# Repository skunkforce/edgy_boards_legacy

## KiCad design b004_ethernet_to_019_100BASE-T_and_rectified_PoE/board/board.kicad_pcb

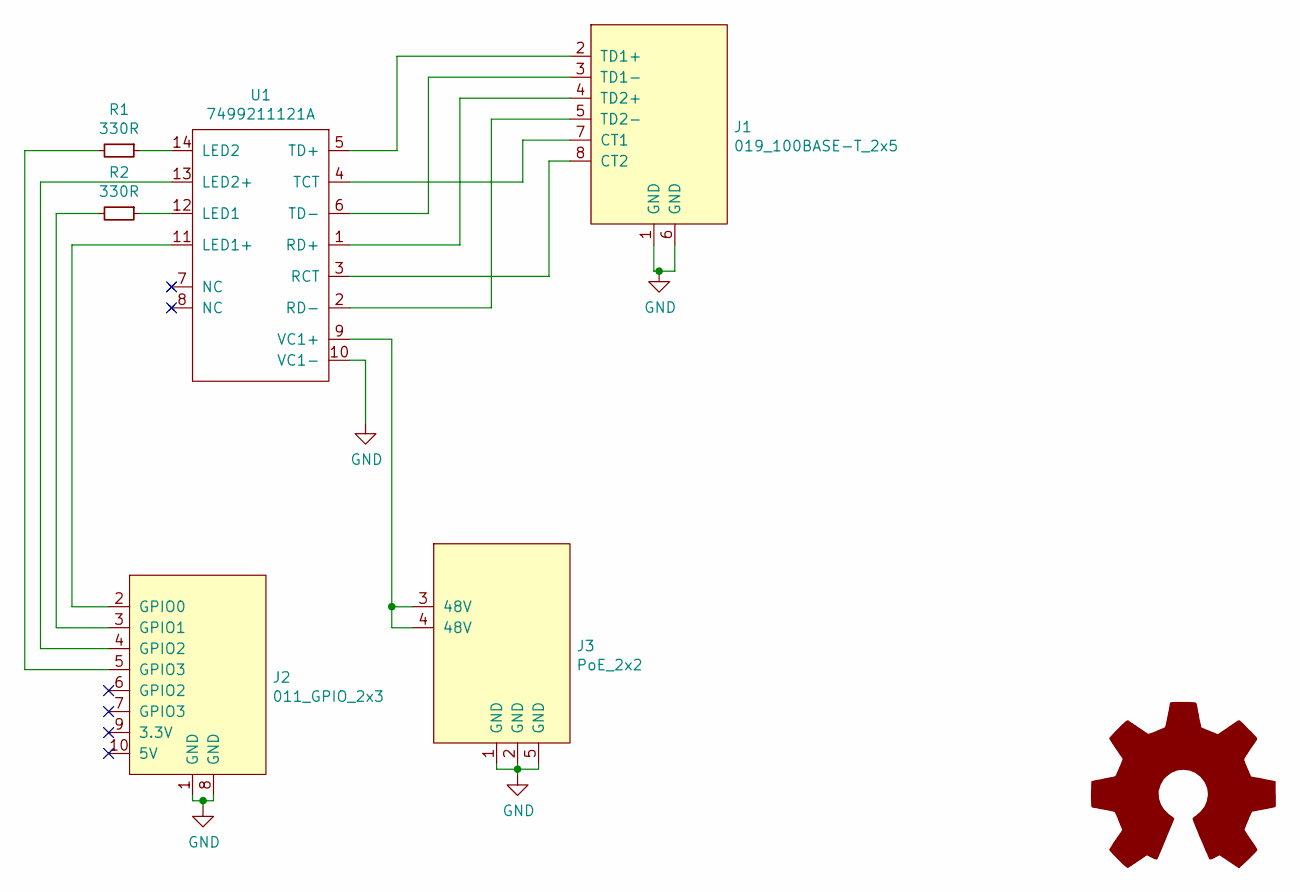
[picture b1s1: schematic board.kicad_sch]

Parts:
J1: 019_100BASE-T_2x5; on_edge_2x05_device
J2: 011_GPIO_2x3; on_edge_2x05_device
J3: PoE_2x2; on_edge_2x05_host
R1, R2: 330R; R_0603_1608Metric
U1: 7499211121A; MPN 7499211121A
l1: Logo_Open_Hardware_Large; OSHW-Logo2_7.3x6mm_SilkScreen

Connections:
GND: J1.1 (GND), J1.6 (GND), J2.1 (GND), J2.8 (GND), J3.1 (GND), J3.2 (GND), J3.5 (GND), U1.10 (VC1-)
unnamed: J1.2 (TD1+), U1.5 (TD+)
unnamed: J1.3 (TD1-), U1.6 (TD-)
unnamed: J1.4 (TD2+), U1.1 (RD+)
unnamed: J1.5 (TD2-), U1.2 (RD-)
unnamed: J1.7 (CT1), U1.4 (TCT)
unnamed: J1.8 (CT2), U1.3 (RCT)
unnamed: J2.2 (GPIO0), U1.11 (LED1+)
unnamed: J2.3 (GPIO1), R2.2
unnamed: J2.4 (GPIO2), U1.13 (LED2+)
unnamed: J2.5 (GPIO3), R1.2
unnamed: J3.3 (48V), J3.4 (48V), U1.9 (VC1+)
unnamed: R1.1, U1.14 (LED2)
unnamed: R2.1, U1.12 (LED1)

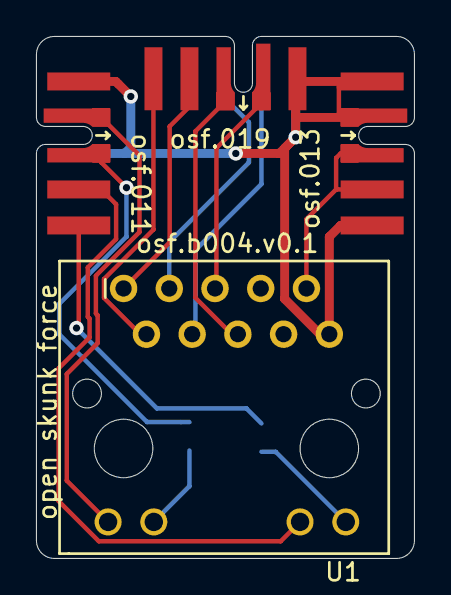
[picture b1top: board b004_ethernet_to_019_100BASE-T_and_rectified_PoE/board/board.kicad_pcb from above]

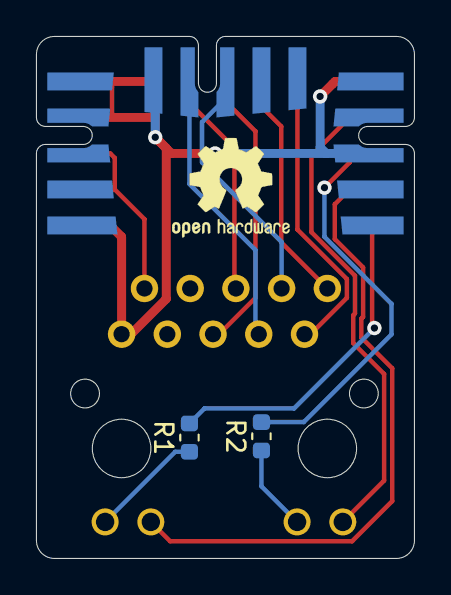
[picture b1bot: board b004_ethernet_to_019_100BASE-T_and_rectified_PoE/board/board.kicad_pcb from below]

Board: 2 copper layers, 21.0 x 29.0 mm, 7 parts (3 on the bottom side), 14 nets.

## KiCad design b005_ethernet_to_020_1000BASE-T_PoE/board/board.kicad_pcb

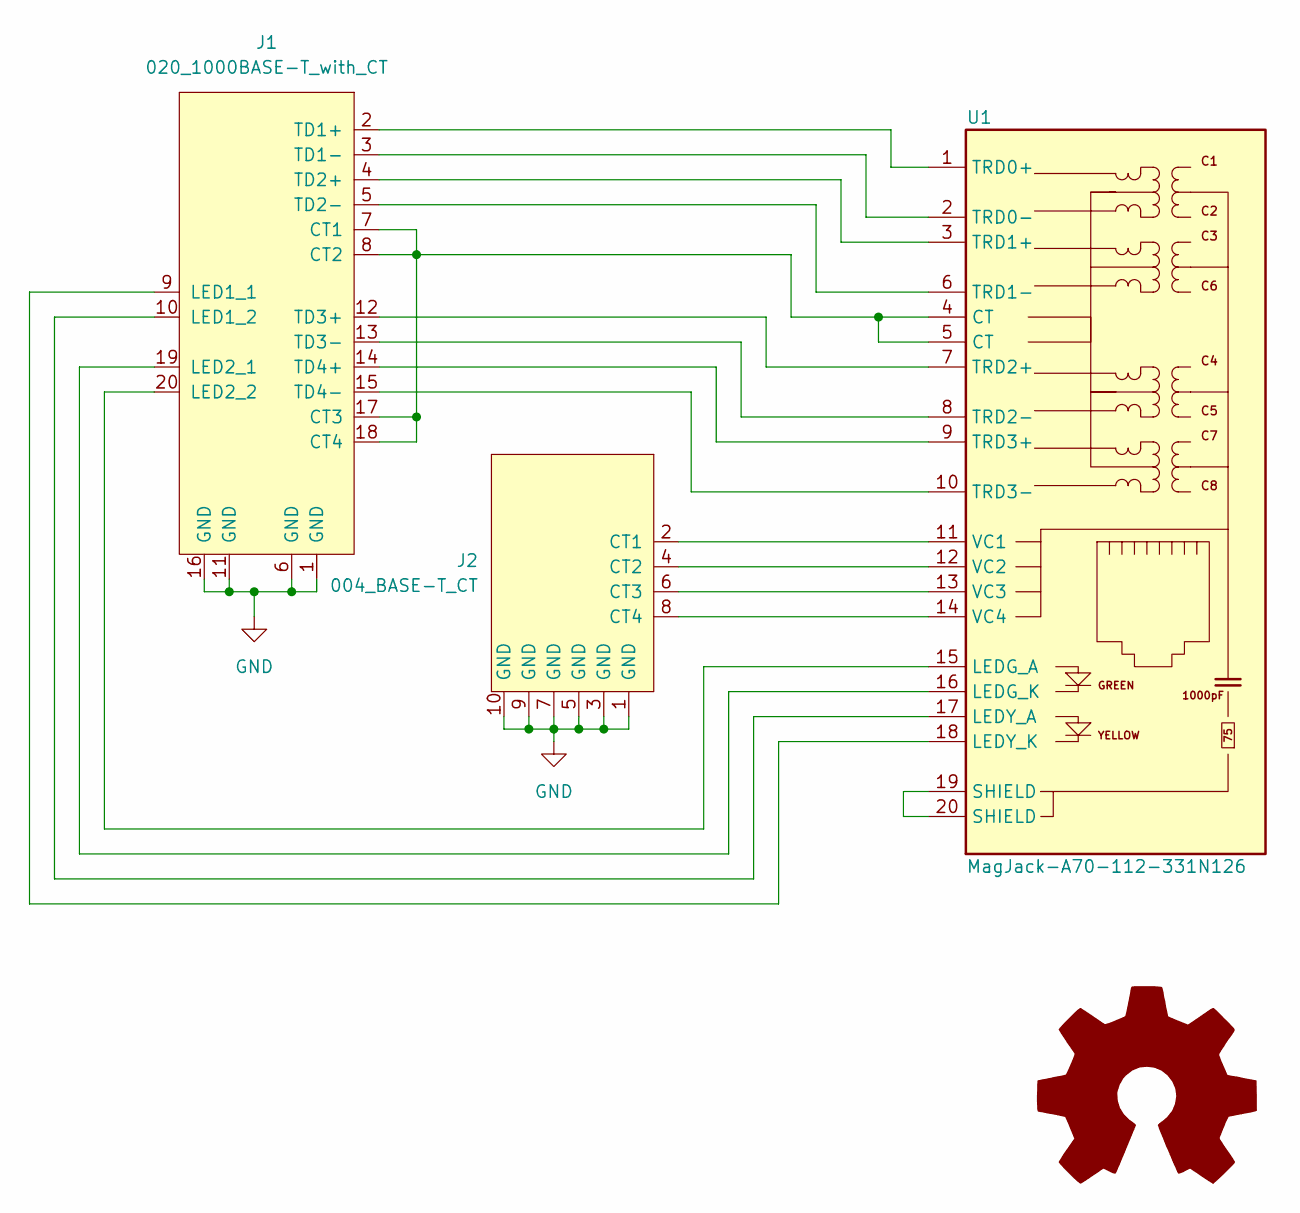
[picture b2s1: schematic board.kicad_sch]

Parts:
J1: 020_1000BASE-T_with_CT; on_edge_2x10_device
J2: 004_BASE-T_CT; on_edge_2x05_host
U1: MagJack-A70-112-331N126; TRJG0926HENL; Part Description Gigabit Ethernet Magjack
l1: Logo_Open_Hardware_Large; OSHW-Logo2_7.3x6mm_SilkScreen

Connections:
GND: J1.1 (GND), J1.6 (GND), J1.11 (GND), J1.16 (GND), J2.1 (GND), J2.3 (GND), J2.5 (GND), J2.7 (GND), J2.9 (GND), J2.10 (GND)
unnamed: J1.2 (TD1+), U1.1 (TRD0+)
unnamed: J1.3 (TD1-), U1.2 (TRD0-)
unnamed: J1.4 (TD2+), U1.3 (TRD1+)
unnamed: J1.5 (TD2-), U1.6 (TRD1-)
unnamed: J1.9 (LED1_1), U1.18 (LEDY_K)
unnamed: J1.10 (LED1_2), U1.17 (LEDY_A)
unnamed: J1.12 (TD3+), U1.7 (TRD2+)
unnamed: J1.13 (TD3-), U1.8 (TRD2-)
unnamed: J1.14 (TD4+), U1.9 (TRD3+)
unnamed: J1.15 (TD4-), U1.10 (TRD3-)
unnamed: J1.7 (CT1), J1.8 (CT2), J1.17 (CT3), J1.18 (CT4), U1.4 (CT), U1.5 (CT)
unnamed: J1.19 (LED2_1), U1.16 (LEDG_K)
unnamed: J1.20 (LED2_2), U1.15 (LEDG_A)
unnamed: J2.2 (CT1), U1.11 (VC1)
unnamed: J2.4 (CT2), U1.12 (VC2)
unnamed: J2.6 (CT3), U1.13 (VC3)
unnamed: J2.8 (CT4), U1.14 (VC4)
unnamed: U1.19 (SHIELD), U1.20 (SHIELD)

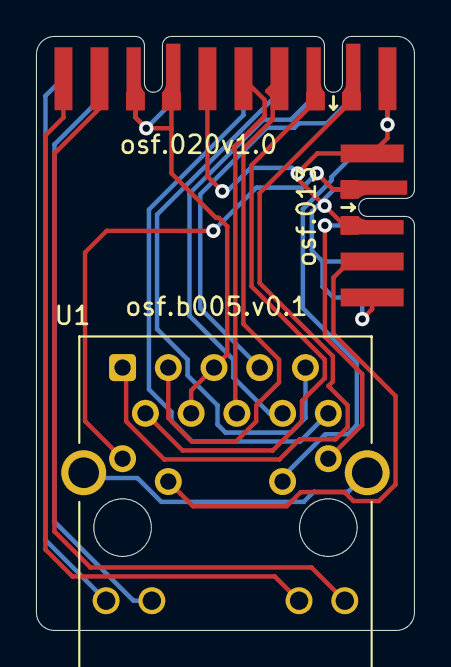
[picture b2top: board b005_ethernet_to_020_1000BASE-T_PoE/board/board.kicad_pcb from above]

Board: 2 copper layers, 21.0 x 33.0 mm, 4 parts (1 on the bottom side), 19 nets.

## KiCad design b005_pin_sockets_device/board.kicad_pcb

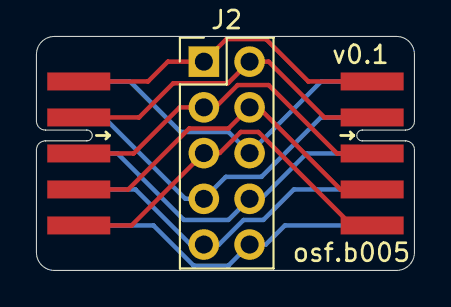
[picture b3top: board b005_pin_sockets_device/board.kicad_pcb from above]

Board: 4 copper layers, 21.0 x 13.0 mm, 3 parts (0 on the bottom side), 10 nets.

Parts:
J1: Conn_01x10_Male; on_edge_2x05_device
J2: CA2310PA10Z; PinHeader_2x05_P2.54mm_Vertical
J6: Conn_01x10_Male; on_edge_2x05_host

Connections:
unnamed: J1.1, J2.1, J6.1
unnamed: J1.2, J2.2, J6.2
unnamed: J1.3, J2.3, J6.3
unnamed: J1.4, J2.4, J6.4
unnamed: J1.5, J2.5, J6.5
unnamed: J1.6, J2.6, J6.6
unnamed: J1.7, J2.7, J6.7
unnamed: J1.8, J2.8, J6.8
unnamed: J1.9, J2.9, J6.9
unnamed: J1.10, J2.10, J6.10

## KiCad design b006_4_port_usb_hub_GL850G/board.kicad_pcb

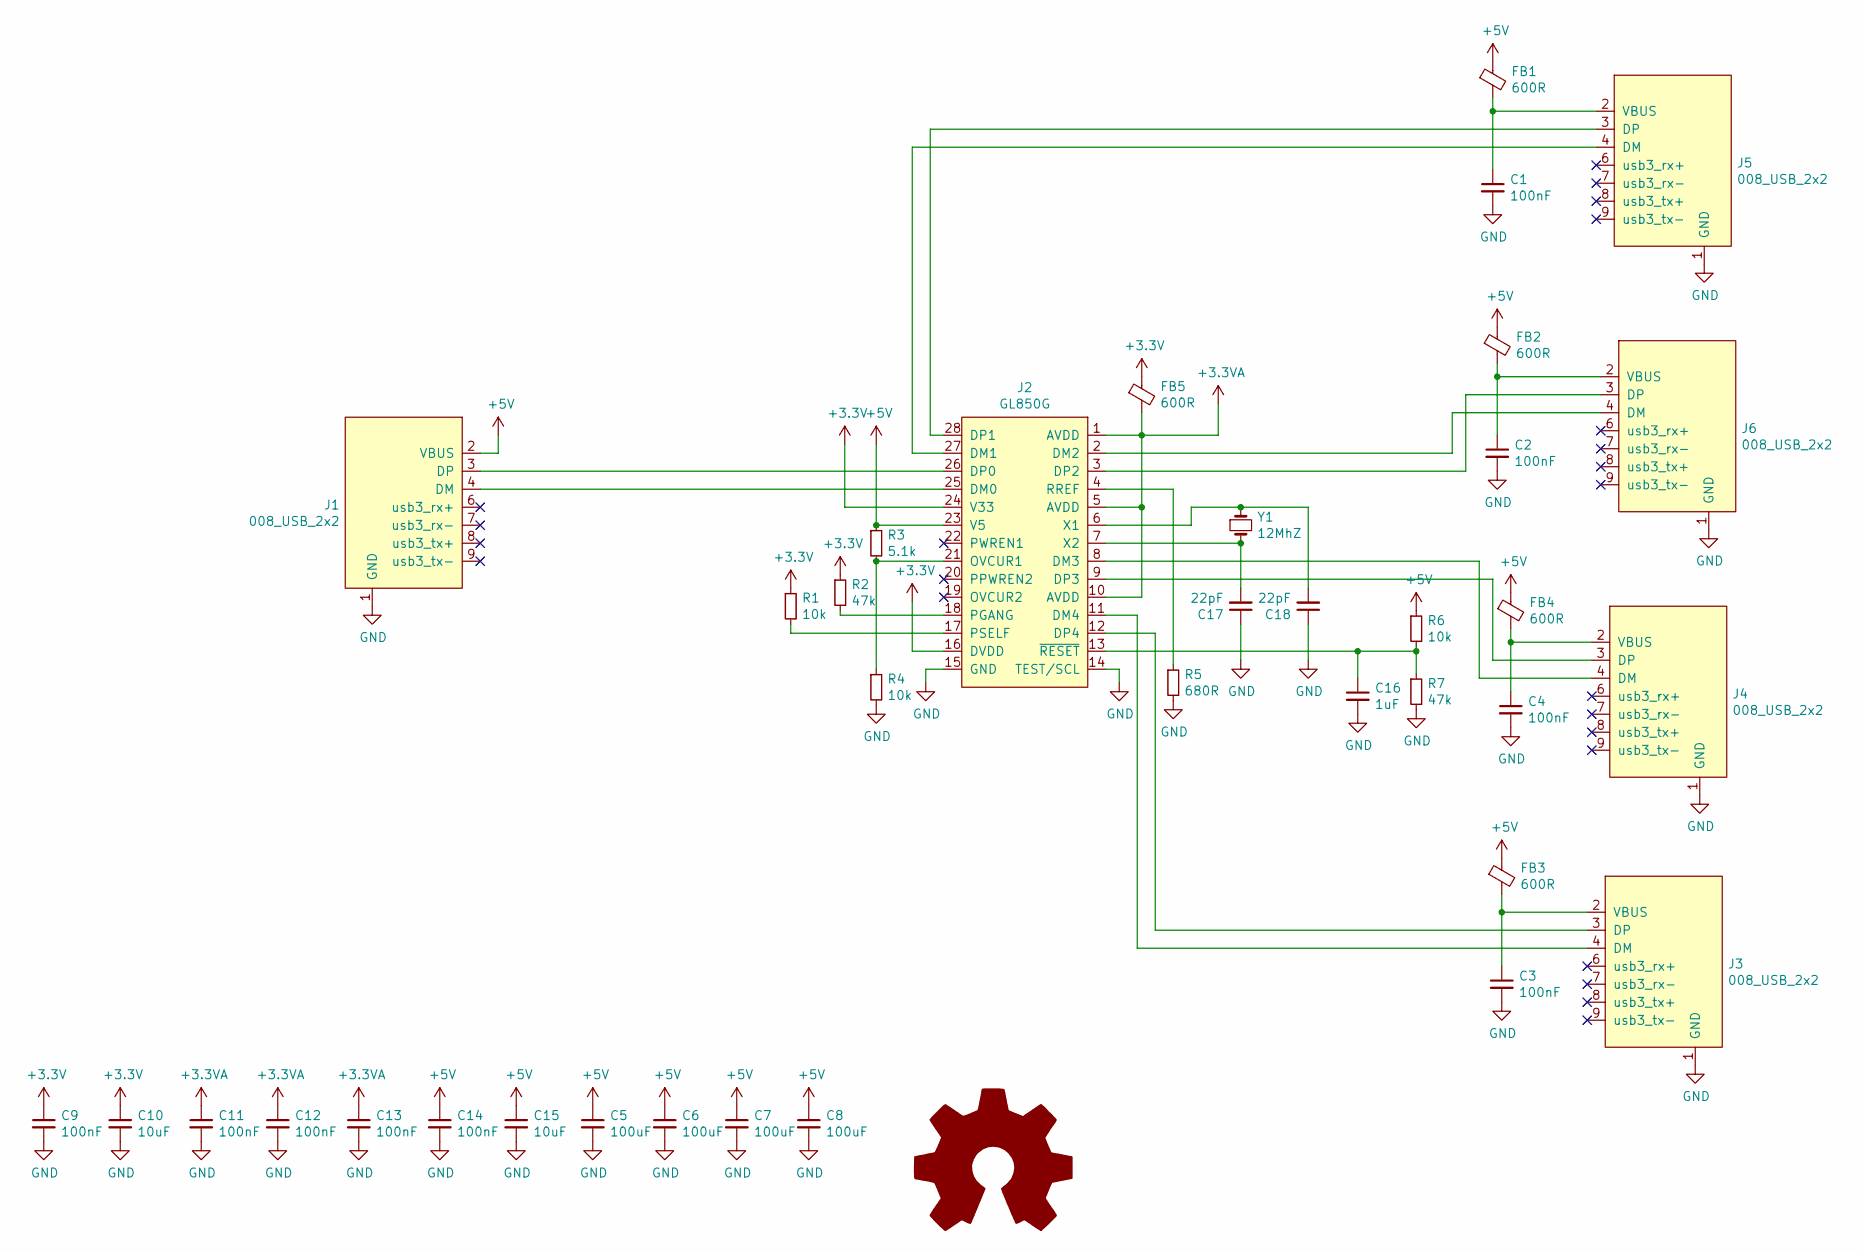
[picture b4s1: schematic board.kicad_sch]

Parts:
C1, C2, C3, C4, C9, C11, C12, C13, C14: 100nF; C_0603_1608Metric
C5, C6, C7, C8: 100uF; C_1210_3225Metric; Voltage 6.3V; MPN 885012109004; Digi-Key_PN 732-7375-1-ND
C10, C15: 10uF; C_0805_2012Metric; Voltage 6.3V
C16: 1uF; C_0603_1608Metric
C17, C18: 22pF; C_0603_1608Metric
FB1, FB2, FB3, FB4, FB5: 600R; L_0805_2012Metric; MPN 742792040
J1: 008_USB_2x2; on_edge_2x05_device
J2: GL850G; SSOP-28_5.3x10.2mm_P0.65mm; MPN GL850G
J3, J4, J5, J6: 008_USB_2x2; on_edge_2x05_host
R1, R4, R6: 10k; R_0603_1608Metric
R2, R7: 47k; R_0603_1608Metric
R3: 5.1k; R_0603_1608Metric
R5: 680R; R_0603_1608Metric
Y1: 12MhZ; Crystal_SMD_7050-2Pin_7.0x5.0mm; MPN NX8045GB-12.000000MHZ
l1: Logo_Open_Hardware_Large; OSHW-Logo2_7.3x6mm_SilkScreen

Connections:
+3.3VA: C11.1, C12.1, C13.1, FB5.2, J2.1 (AVDD), J2.5 (AVDD), J2.10 (AVDD)
+3V3: C9.1, C10.1, FB5.1, J2.16 (DVDD), J2.24 (V33), R1.1, R2.1
+5V: C5.1, C6.1, C7.1, C8.1, C14.1, C15.1, FB1.1, FB2.1, FB3.1, FB4.1, J1.2 (VBUS), J2.23 (V5), R3.1, R6.1
GND: C1.2, C2.2, C3.2, C4.2, C5.2, C6.2, C7.2, C8.2, C9.2, C10.2, C11.2, C12.2, C13.2, C14.2, C15.2, C16.2, C17.1, C18.1, J1.1 (GND), J2.14 (TEST/SCL), J2.15 (GND), J3.1 (GND), J4.1 (GND), J5.1 (GND), J6.1 (GND), R4.2, R5.2, R7.2
unnamed: C1.1, FB1.2, J5.2 (VBUS)
unnamed: C2.1, FB2.2, J6.2 (VBUS)
unnamed: C3.1, FB3.2, J3.2 (VBUS)
unnamed: C4.1, FB4.2, J4.2 (VBUS)
unnamed: C16.1, J2.13 (~RESET), R6.2, R7.1
unnamed: C17.2, J2.7 (X2), Y1.2
unnamed: C18.2, J2.6 (X1), Y1.1
unnamed: J1.3 (DP), J2.26 (DP0)
unnamed: J1.4 (DM), J2.25 (DM0)
unnamed: J2.2 (DM2), J6.4 (DM)
unnamed: J2.3 (DP2), J6.3 (DP)
unnamed: J2.4 (RREF), R5.1
unnamed: J2.8 (DM3), J4.4 (DM)
unnamed: J2.9 (DP3), J4.3 (DP)
unnamed: J2.11 (DM4), J3.4 (DM)
unnamed: J2.12 (DP4), J3.3 (DP)
unnamed: J2.17 (PSELF), R1.2
unnamed: J2.18 (PGANG), R2.2
unnamed: J2.21 (OVCUR1), R3.2, R4.1
unnamed: J2.27 (DM1), J5.4 (DM)
unnamed: J2.28 (DP1), J5.3 (DP)

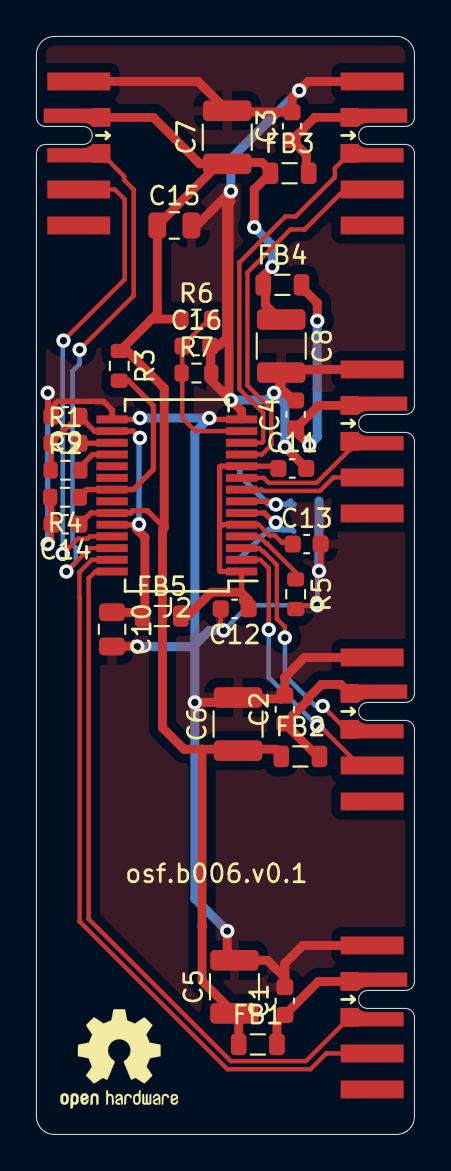
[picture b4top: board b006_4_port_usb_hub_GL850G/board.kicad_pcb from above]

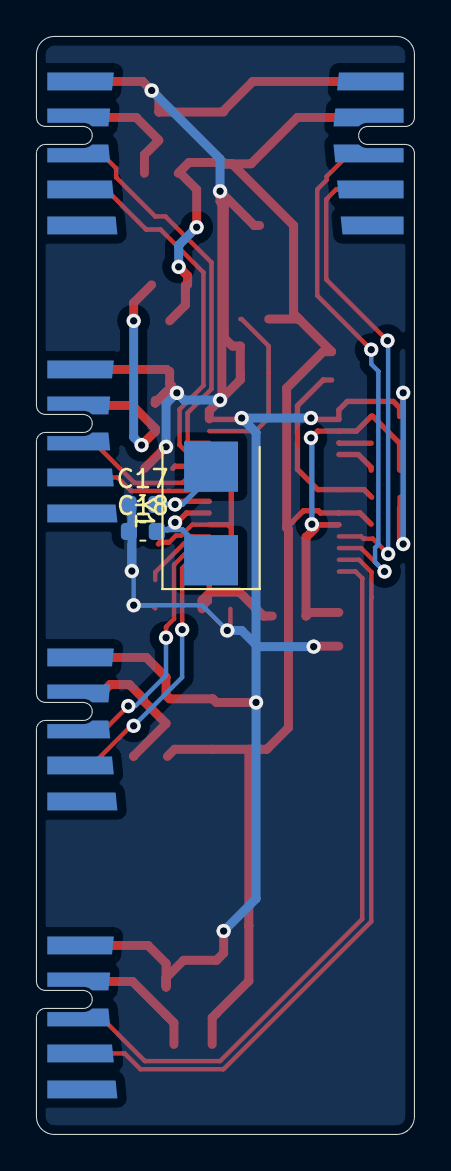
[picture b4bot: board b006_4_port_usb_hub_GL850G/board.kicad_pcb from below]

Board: 2 copper layers, 21.0 x 61.0 mm, 38 parts (3 on the bottom side), 25 nets.

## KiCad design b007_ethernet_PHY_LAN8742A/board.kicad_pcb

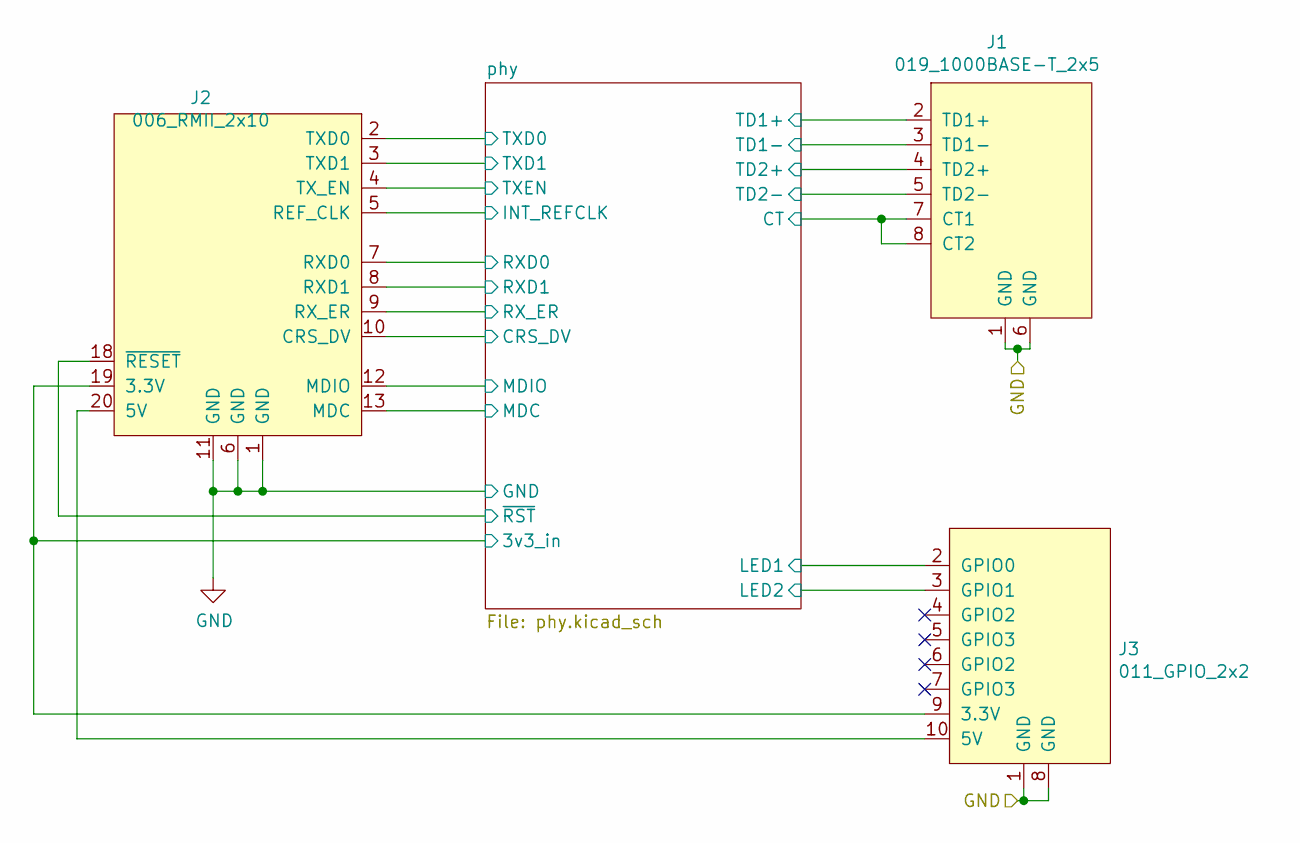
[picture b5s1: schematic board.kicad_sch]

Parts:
J1: 019_1000BASE-T_2x5; on_edge_2x05_host
J2: 006_RMII_2x10; on_edge_2x10_device
J3: 011_GPIO_2x2; on_edge_2x05_host

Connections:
/phy/3v3_in: J2.19 (3.3V), J3.9 (3.3V); also elsewhere on the board
/phy/CRS_DV: J2.10 (CRS_DV); also elsewhere on the board
/phy/ETH_VDD: J1.7 (CT1), J1.8 (CT2); also elsewhere on the board
/phy/INT_REFCLK: J2.5 (REF_CLK); also elsewhere on the board
/phy/LED1: J3.2 (GPIO0); also elsewhere on the board
/phy/LED2: J3.3 (GPIO1); also elsewhere on the board
/phy/MDC: J2.13 (MDC); also elsewhere on the board
/phy/MDIO: J2.12 (MDIO); also elsewhere on the board
/phy/RXD0: J2.7 (RXD0); also elsewhere on the board
/phy/RXD1: J2.8 (RXD1); also elsewhere on the board
/phy/RX_ER: J2.9 (RX_ER); also elsewhere on the board
/phy/TD1+: J1.2 (TD1+); also elsewhere on the board
/phy/TD1-: J1.3 (TD1-); also elsewhere on the board
/phy/TD2+: J1.4 (TD2+); also elsewhere on the board
/phy/TD2-: J1.5 (TD2-); also elsewhere on the board
/phy/TXD0: J2.2 (TXD0); also elsewhere on the board
/phy/TXD1: J2.3 (TXD1); also elsewhere on the board
/phy/TXEN: J2.4 (TX_EN); also elsewhere on the board
/phy/~RST: J2.18 (~RESET); also elsewhere on the board
GND: J1.1 (GND), J1.6 (GND), J2.1 (GND), J2.6 (GND), J2.11 (GND), J3.1 (GND), J3.8 (GND); also elsewhere on the board
unnamed: J2.20 (5V), J3.10 (5V)

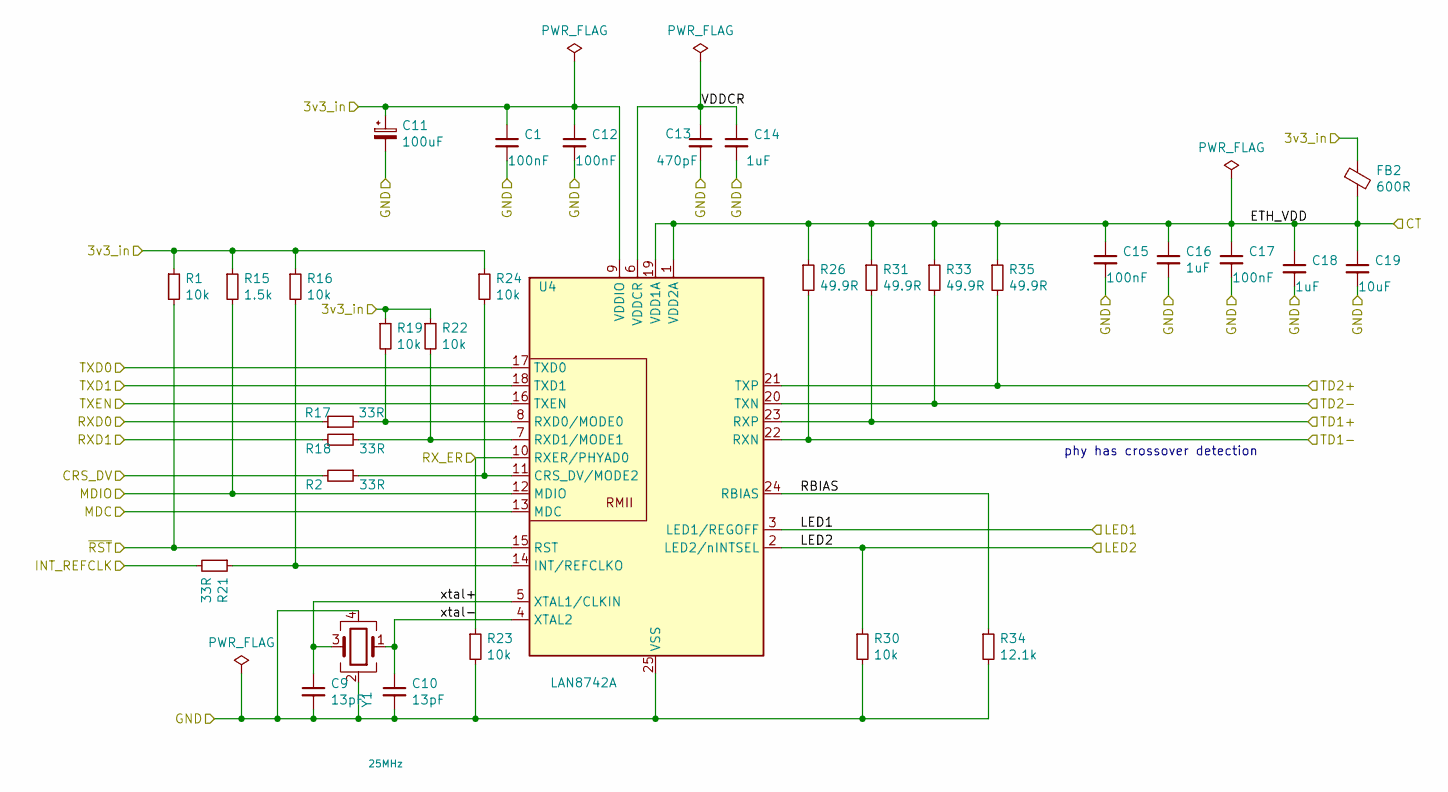
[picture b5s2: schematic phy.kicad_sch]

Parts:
C1, C12, C15, C17: 100nF; C_0603_1608Metric
C9, C10: 13pF; C_0603_1608Metric
C11: 100uF; C_1210_3225Metric
C13: 470pF; C_0603_1608Metric
C14, C16, C18: 1uF; C_0603_1608Metric
C19: 10uF; C_0805_2012Metric
FB2: 600R; L_0805_2012Metric
R1, R16, R19, R22, R23, R24, R30: 10k; R_0603_1608Metric
R2, R17, R18, R21: 33R; R_0603_1608Metric
R15: 1.5k; R_0603_1608Metric
R26, R31, R33, R35: 49.9R; R_0603_1608Metric
R34: 12.1k; R_0603_1608Metric
U4: LAN8742A; QFN-24-1EP_4x4mm_P0.5mm_EP2.6x2.6mm; Digi-Key_PN LAN8742A
Y1: 25MHz; Crystal_SMD_Abracon_ABM8G-4Pin_3.2x2.5mm; Digi-Key_PN 535-9140-1-ND

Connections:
/phy/3v3_in: C1.1, C11.1, C12.1, FB2.1, R1.1, R15.1, R16.1, R19.1, R22.1, R24.1, U4.9 (VDDIO); also elsewhere on the board
/phy/CRS_DV: R2.2; also elsewhere on the board
/phy/ETH_VDD: C15.1, C16.1, C17.1, C18.1, C19.1, FB2.2, R26.1, R31.1, R33.1, R35.1, U4.1 (VDD2A), U4.19 (VDD1A); also elsewhere on the board
/phy/INT_REFCLK: R21.2; also elsewhere on the board
/phy/LED1: U4.3 (LED1/REGOFF); also elsewhere on the board
/phy/LED2: R30.1, U4.2 (LED2/nINTSEL); also elsewhere on the board
/phy/MDC: U4.13 (MDC); also elsewhere on the board
/phy/MDIO: R15.2, U4.12 (MDIO); also elsewhere on the board
/phy/RBIAS: R34.1, U4.24 (RBIAS)
/phy/RXD0: R17.1; also elsewhere on the board
/phy/RXD1: R18.2; also elsewhere on the board
/phy/RX_ER: R23.1, U4.10 (RXER/PHYAD0); also elsewhere on the board
/phy/TD1+: R31.2, U4.23 (RXP); also elsewhere on the board
/phy/TD1-: R26.2, U4.22 (RXN); also elsewhere on the board
/phy/TD2+: R35.2, U4.21 (TXP); also elsewhere on the board
/phy/TD2-: R33.2, U4.20 (TXN); also elsewhere on the board
/phy/TXD0: U4.17 (TXD0); also elsewhere on the board
/phy/TXD1: U4.18 (TXD1); also elsewhere on the board
/phy/TXEN: U4.16 (TXEN); also elsewhere on the board
/phy/VDDCR: C13.1, C14.1, U4.6 (VDDCR)
/phy/xtal+: C9.1, U4.5 (XTAL1/CLKIN), Y1.3
/phy/xtal-: C10.1, U4.4 (XTAL2), Y1.1
/phy/~RST: R1.2, U4.15 (RST); also elsewhere on the board
GND: C1.2, C9.2, C10.2, C11.2, C12.2, C13.2, C14.2, C15.2, C16.2, C17.2, C18.2, C19.2, R23.2, R30.2, R34.2, U4.25 (VSS), Y1.2, Y1.4; also elsewhere on the board
unnamed: R2.1, R24.2, U4.11 (CRS_DV/MODE2)
unnamed: R16.2, R21.1, U4.14 (INT/REFCLKO)
unnamed: R17.2, R19.2, U4.8 (RXD0/MODE0)
unnamed: R18.1, R22.2, U4.7 (RXD1/MODE1)

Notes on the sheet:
phy has crossover detection

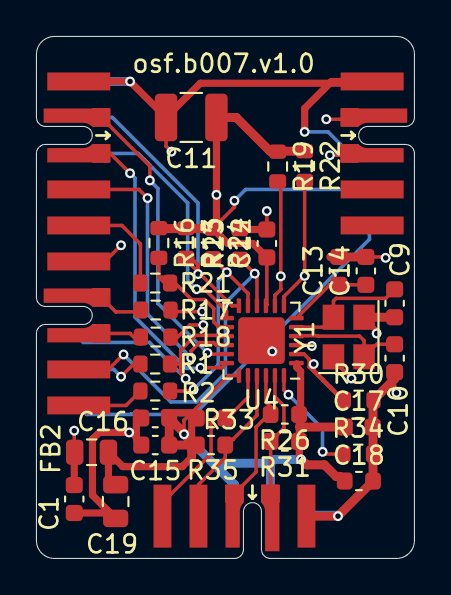
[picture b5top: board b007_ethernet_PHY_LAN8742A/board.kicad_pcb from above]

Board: 4 copper layers, 21.0 x 29.0 mm, 35 parts (0 on the bottom side), 29 nets.

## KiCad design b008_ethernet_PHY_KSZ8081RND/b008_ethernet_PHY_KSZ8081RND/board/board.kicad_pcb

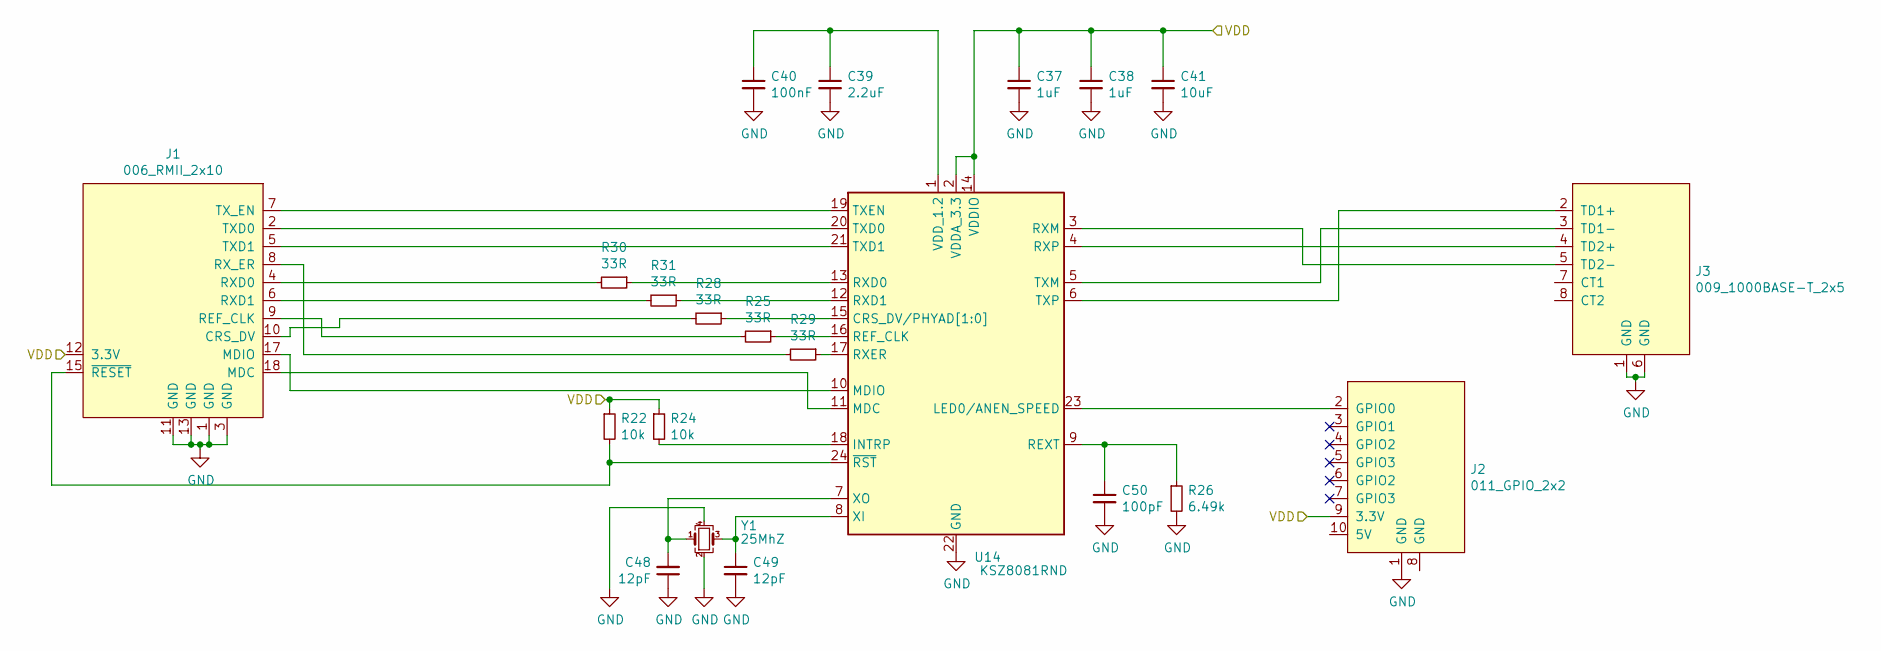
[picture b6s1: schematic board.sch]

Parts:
C37, C38: 1uF; C_0603_1608Metric
C39: 2.2uF; C_0603_1608Metric
C40: 100nF; C_0603_1608Metric
C41: 10uF; C_0603_1608Metric
C48, C49: 12pF; C_0603_1608Metric
C50: 100pF; C_0603_1608Metric
J1: 006_RMII_2x10; on_edge_2x10_device
J2: 011_GPIO_2x2; on_edge_2x05_host
J3: 009_1000BASE-T_2x5; on_edge_2x05_host
R22, R24: 10k; R_0603_1608Metric
R25, R28, R29, R30, R31: 33R; R_0603_1608Metric
R26: 6.49k; R_0603_1608Metric
U14: KSZ8081RND; QFN-24-1EP_4x4mm_P0.5mm_EP2.6x2.6mm; MPN KSZ8081RND
Y1: 25MhZ; Crystal_SMD_Abracon_ABM8G-4Pin_3.2x2.5mm; MPN ‎XC3065CT-ND‎

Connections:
/VDD: C37.1, C38.1, C41.1, J1.12 (3.3V), J2.9 (3.3V), R22.1, R24.1, U14.2 (VDDA_3.3), U14.14 (VDDIO)
GND: C37.2, C38.2, C39.2, C40.2, C41.2, C48.1, C49.2, C50.2, J1.1 (GND), J1.3 (GND), J1.11 (GND), J1.13 (GND), J2.1 (GND), J3.1 (GND), J3.6 (GND), R26.2, U14.22 (GND), U14.25 (GND), Y1.2, Y1.4
unnamed: C39.1, C40.1, U14.1 (VDD_1.2)
unnamed: C48.2, U14.7 (XO), Y1.1
unnamed: C49.1, U14.8 (XI), Y1.3
unnamed: C50.1, R26.1, U14.9 (REXT)
unnamed: J1.2 (TXD0), U14.20 (TXD0)
unnamed: J1.4 (RXD0), R30.2
unnamed: J1.5 (TXD1), U14.21 (TXD1)
unnamed: J1.6 (RXD1), R31.2
unnamed: J1.7 (TX_EN), U14.19 (TXEN)
unnamed: J1.8 (RX_ER), R29.2
unnamed: J1.9 (REF_CLK), R25.2
unnamed: J1.10 (CRS_DV), R28.2
unnamed: J1.15 (~RESET), R22.2, U14.24 (~RST)
unnamed: J1.17 (MDIO), U14.10 (MDIO)
unnamed: J1.18 (MDC), U14.11 (MDC)
unnamed: J2.2 (GPIO0), U14.23 (LED0/ANEN_SPEED)
unnamed: J3.2 (TD1+), U14.6 (TXP)
unnamed: J3.3 (TD1-), U14.5 (TXM)
unnamed: J3.4 (TD2+), U14.4 (RXP)
unnamed: J3.5 (TD2-), U14.3 (RXM)
unnamed: R24.2, U14.18 (INTRP)
unnamed: R25.1, U14.16 (REF_CLK)
unnamed: R28.1, U14.15 (CRS_DV/PHYAD[1:0])
unnamed: R29.1, U14.17 (RXER)
unnamed: R30.1, U14.13 (RXD0)
unnamed: R31.1, U14.12 (RXD1)

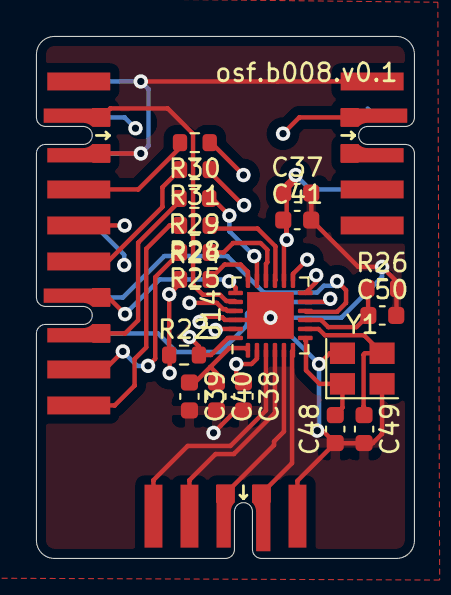
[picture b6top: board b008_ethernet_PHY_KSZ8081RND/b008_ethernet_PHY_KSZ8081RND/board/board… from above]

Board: 4 copper layers, 21.0 x 29.0 mm, 21 parts (0 on the bottom side), 28 nets.

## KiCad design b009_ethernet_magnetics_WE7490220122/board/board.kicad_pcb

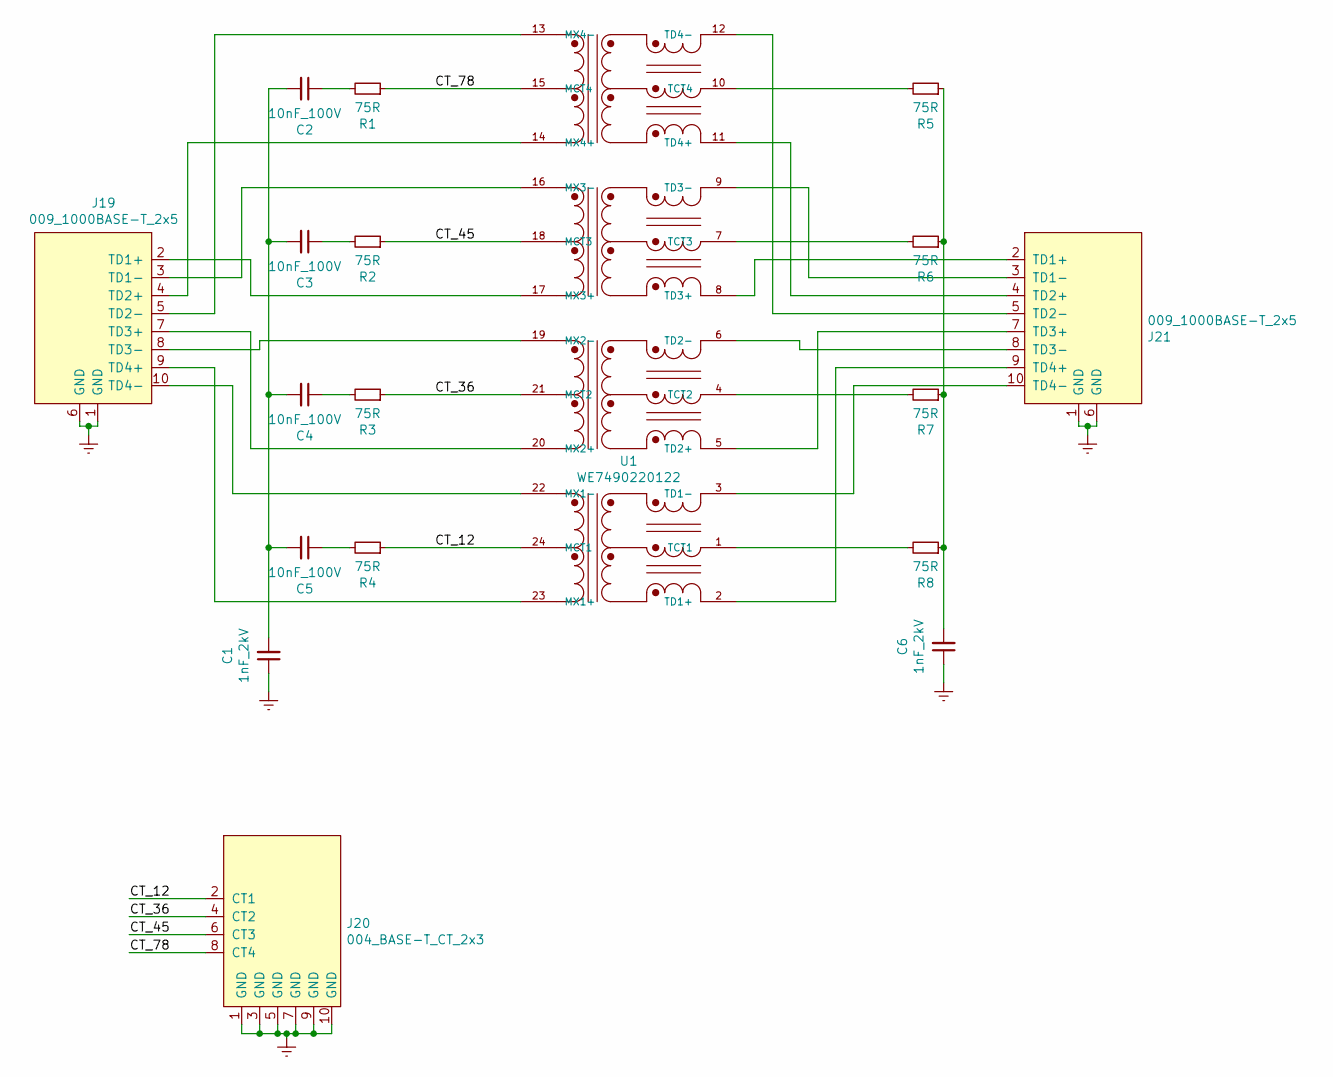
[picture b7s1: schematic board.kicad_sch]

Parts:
C1, C6: 1nF_2kV; C_1210_3225Metric; Voltage 2000; MPN CL32B102KJFNNNE
C2, C3, C4, C5: 10nF_100V; C_0603_1608Metric; Voltage 100; MPN ‎CL10B103KC8NNNC‎
J19: 009_1000BASE-T_2x5; on_edge_2x05_host
J20: 004_BASE-T_CT_2x3; on_edge_2x05_host
J21: 009_1000BASE-T_2x5; on_edge_2x05_device
R1, R2, R3, R4, R5, R6, R7, R8: 75R; R_0805_2012Metric; MPN ‎RMCF0805FT75R0‎
U1: WE7490220122; XFMR_7490220122; MPN 7490220122; Digi-Key_PN 732-10731-1-ND

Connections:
/CT_12: J20.2 (CT1), R4.1, U1.24 (MCT1)
/CT_36: J20.4 (CT2), R3.1, U1.21 (MCT2)
/CT_45: J20.6 (CT3), R2.1, U1.18 (MCT3)
/CT_78: J20.8 (CT4), R1.1, U1.15 (MCT4)
Earth: C1.1, C6.1, J19.1 (GND), J19.6 (GND), J20.1 (GND), J20.3 (GND), J20.5 (GND), J20.7 (GND), J20.9 (GND), J20.10 (GND), J21.1 (GND), J21.6 (GND)
unnamed: C1.2, C2.2, C3.2, C4.2, C5.2
unnamed: C3.1, R2.2
unnamed: C5.1, R4.2
unnamed: C2.1, R1.2
unnamed: C4.1, R3.2
unnamed: C6.2, R5.1, R6.1, R7.1, R8.1
unnamed: R5.2, U1.10 (TCT4)
unnamed: R8.2, U1.1 (TCT1)
unnamed: J21.9 (TD4+), U1.2 (TD1+)
unnamed: J21.10 (TD4-), U1.3 (TD1-)
unnamed: R7.2, U1.4 (TCT2)
unnamed: J21.7 (TD3+), U1.5 (TD2+)
unnamed: J21.8 (TD3-), U1.6 (TD2-)
unnamed: R6.2, U1.7 (TCT3)
unnamed: J21.2 (TD1+), U1.8 (TD3+)
unnamed: J21.3 (TD1-), U1.9 (TD3-)
unnamed: J21.4 (TD2+), U1.11 (TD4+)
unnamed: J21.5 (TD2-), U1.12 (TD4-)
unnamed: J19.5 (TD2-), U1.13 (MX4-)
unnamed: J19.4 (TD2+), U1.14 (MX4+)
unnamed: J19.3 (TD1-), U1.16 (MX3-)
unnamed: J19.2 (TD1+), U1.17 (MX3+)
unnamed: J19.8 (TD3-), U1.19 (MX2-)
unnamed: J19.7 (TD3+), U1.20 (MX2+)
unnamed: J19.10 (TD4-), U1.22 (MX1-)
unnamed: J19.9 (TD4+), U1.23 (MX1+)

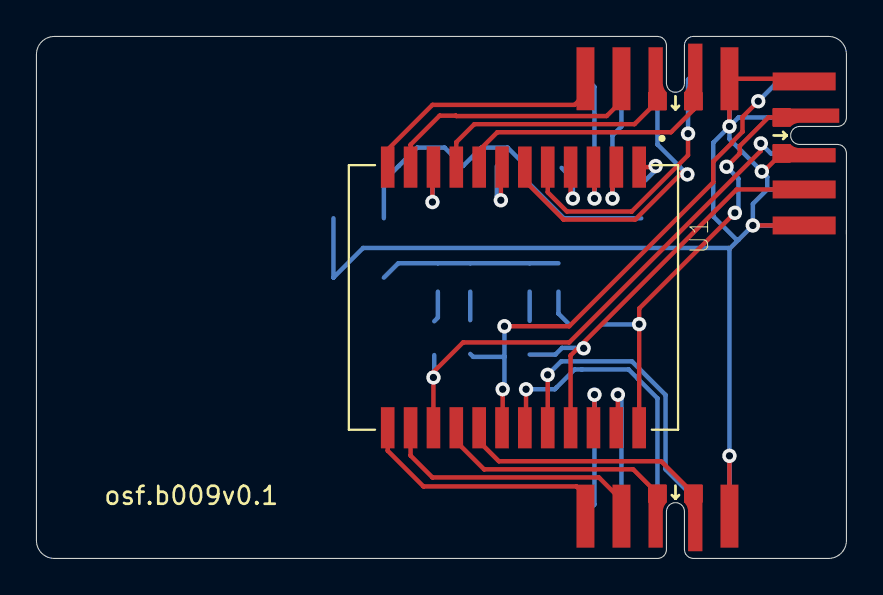
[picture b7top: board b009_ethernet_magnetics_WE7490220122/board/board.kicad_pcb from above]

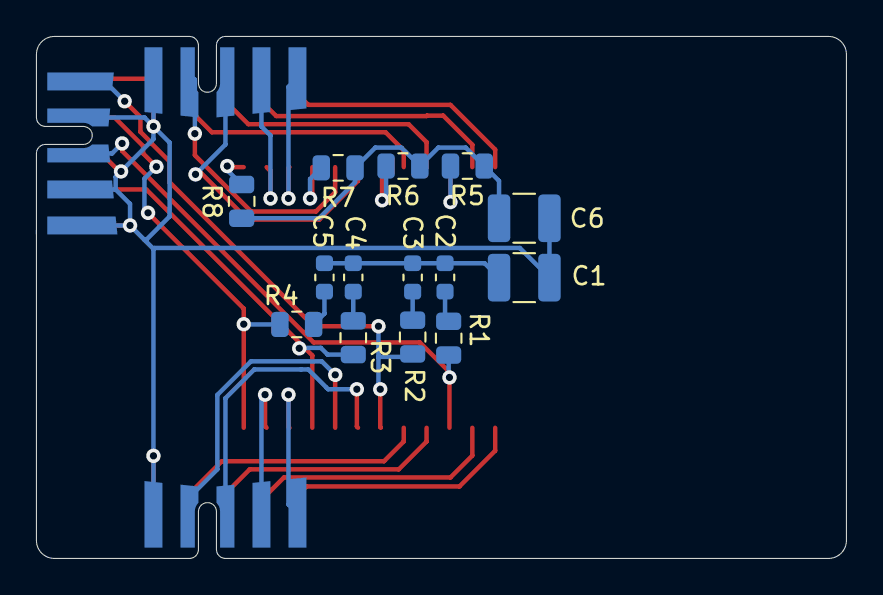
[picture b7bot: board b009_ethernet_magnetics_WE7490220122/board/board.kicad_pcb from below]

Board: 2 copper layers, 45.0 x 29.0 mm, 18 parts (14 on the bottom side), 31 nets.
